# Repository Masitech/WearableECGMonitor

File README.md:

# WearableECGMonitor

Project Report (110 pages) : https://www.mahmed.tech/wp-content/uploads/2020/05/Project_Report_MAhmed-converted-compressed.pdf 

## 1.1 Background

The IoT (internet of things) field in wearable healthcare has received a lot of attention in the last
few years due to advancement in computing paradigms: cloud computing, fog computing and
edge computing. Machine learning on the cloud has revolutionized traditional healthcare.
ECG monitors is not a new concept, it has been around the medical environment for many
decades. In the last few years, technology has started appearing in many wearable devices such
as smartwatches (apple watch 4+) and dedicated standalone products such as AliveCor's
KardiaMobile[3]. Most of the designs use 3 wires: 2 wires for bipotential input and the third wire
for body bias (common-mode rejection).

## 1.2 Aim

This project aims to design a low power battery operated wearable device with wireless
capability that can measure ECG from the bipotential single channel. The system should be
lightweight and small since it will be worn for a long period without a battery recharge.
Use professional tools & software platforms to design the system which is relevant in the
embedded systems industry.
Understand low level embedded systems and overcome problems which are specific to the
project using OEM datasheet/documentation. 

## 1.3 Objective

* Small custom-designed embedded arm cortex board using small SMD parts (0603 or
smaller).

* Develop low power wearable hardware that can be powered from a small battery.

* Develop onboard battery management system for charging lipo battery.

* Implement low power wireless capability using BLE.

* Design and implement embedded firmware using RTOS

* Use of UART, SPI, PWM, SAADC, Timers and interrupts in the firmware using
low-level hardware coding and API.

* Use of commercial development software and tools.

## 1.4 Technical Requirement / Tools

During the development phase of this project, the following tools were used, and it would be
essential to have access to these tools for future continuation of the work.

Software IDE: Keil uVision 5 

JLink Debugger / STLink Programmer: Used to flash the microcontroller.

J-Flash Light v6.54 (Tool to flash hex file)

nRF Bluetooth Connect App for Bluetooth Debugging (Android)

FTDI (USB to Serial) Module - UART communication

Eagle Autodesk to modify the schematic

Embedded C++/C, JavaScript, Bluetooth GATT, Max30003 AFE, Mbed OS, nrfSDK15

Optional: Tools that can be helpful.

SamacSys PCB Library: Excellent tool to get component footprint and save time

Notepad++ : Generic text editor, highly recommended

UART serial monitor: Arduino Serial Monitor, Termite

Plotting ECG Waveform: Arduino Plotter, Windisp (Custom Tool)

Multimeter, Oscilloscope & SMD soldering skills 

## 2. System Design

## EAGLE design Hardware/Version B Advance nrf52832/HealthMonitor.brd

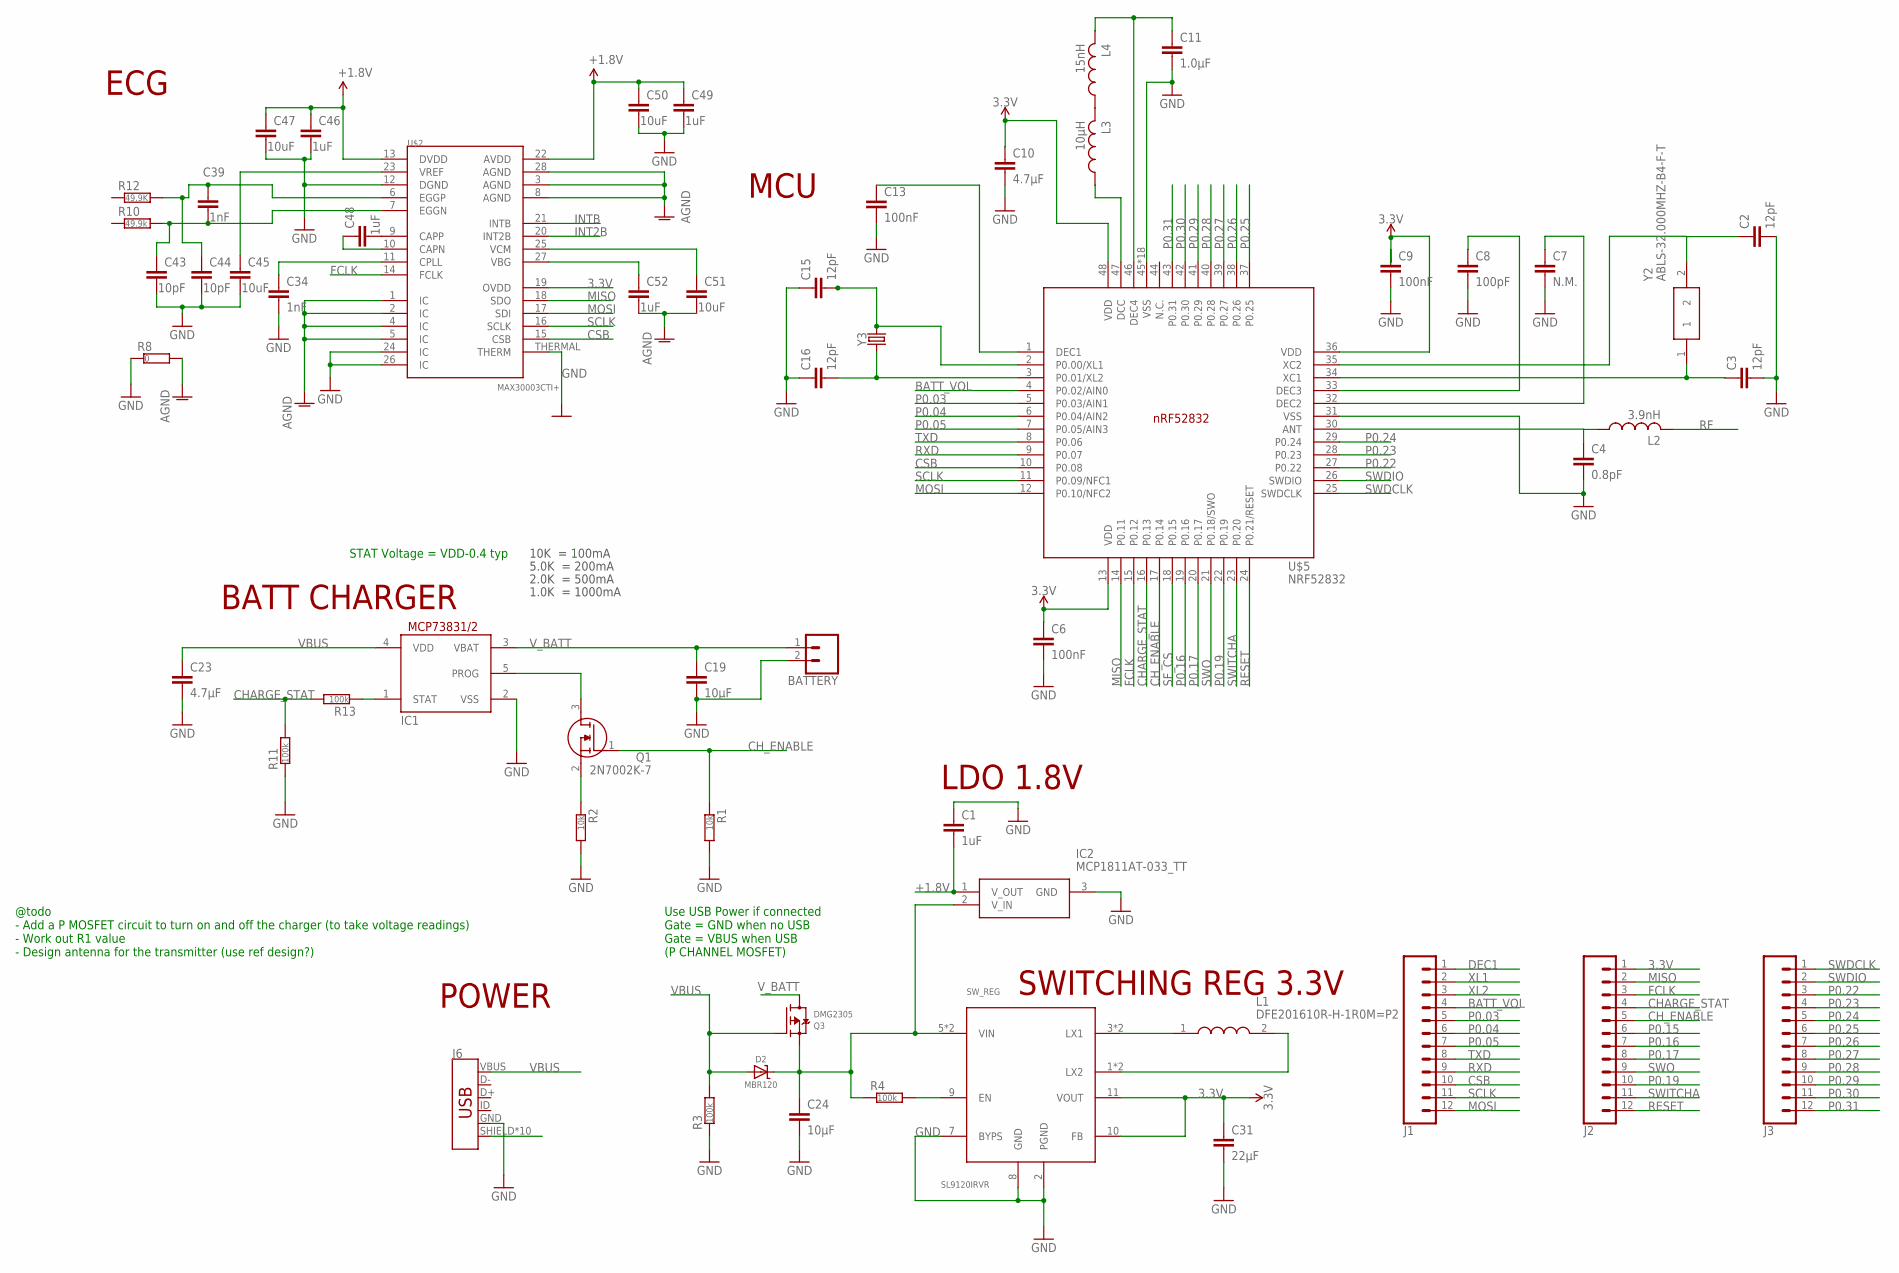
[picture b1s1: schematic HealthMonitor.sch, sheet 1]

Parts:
BATTERY: CONN_02; 1X02
C1: 1uF; RESC0603_L
C2, C3, C15, C16: 12pF; RESC0603_L
C4: 0.8pF; RESC0603_L
C6, C9, C13: 100nF; RESC0603_L
C7: N.M.; RESC0603_L
C8: 100pF; RESC0603_L
C10, C23: 4.7µF; RESC0603_N
C11: 1.0µF; RESC0603_N
C19, C24: 10µF; RESC0603_N
C31: 22µF; RESC0603_N
C34: 1nF; C0603
C39: 1nF; RESC0603_N
C43, C44: 10pF; RESC0603_N
C45, C47, C50, C51: 10uF; RESC0603_N
C46, C48, C49, C52: 1uF; RESC0603_N
D2: MBR120; SOD-123
IC1: MCP73831/OT; SOT23-5L
IC2: MCP1811AT-033_TT; SOT95P237X112-3N
J1, J2, J3: CONN_12; 1X12
J6: USB_MICRO-B_HALF_PTH_MILL; USB-MICROB-PTH-MILL
L1: DFE201610R-H-1R0M=P2; INDC2016X100N
L2: 3.9nH; RESC0402_N
L3: 10µH; RESC0603_N
L4: 15nH; RESC0402_N
Q1: 2N7002K-7; SOT96P240X100-3N
Q3: DMG2305; SOT23-R
R1, R2: 10k; RESC0603_L
R3, R4, R11, R13: 100k; RESC0603_L
R8: 0; RESC0603_L
R10: 49.9k; RESC0603_L
R12: 49.9K; RESC0603_L
SW_REG: SL9120IRVR; TQFN-12
U$2: MAX30003CTI+; QFN-28
U$5: NRF52832; QFN40P600X600X90-48_N
Y2: ABLS-32.000MHZ-B4-F-T; ABLS-12.000MHZ-B2
Y3: CRYSTALSMD-2X6; CRYSTAL-SMD-2X6-CYL

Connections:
3.3V: C6.1, C9.1, C10.1, C31.1, J2.1, SW_REG.10 (FB), SW_REG.11 (VOUT), U$2.19 (OVDD), U$5.13 (VDD), U$5.36 (VDD), U$5.48 (VDD); also elsewhere on the board
+1.8V: C1.2, C46.1, C47.1, C49.1, C50.1, IC2.1 (V_OUT), U$2.13 (DVDD), U$2.22 (AVDD); also elsewhere on the board
AGND: C51.2, C52.2, R8.2, U$2.1 (IC), U$2.2 (IC), U$2.3 (AGND), U$2.4 (IC), U$2.5 (IC), U$2.8 (AGND), U$2.28 (AGND)
BATT_VOL: J1.4, U$5.4 (P0.02/AIN0); also elsewhere on the board
CHARGE_STAT: J2.4, R11.2, R13.2, U$5.16 (P0.13)
CH_ENABLE: J2.5, Q1.1 (G), R1.1, U$5.17 (P0.14)
CSB: J1.10, U$2.15 (CSB), U$5.10 (P0.08)
DEC1: J1.1
ECGN1: C39.2, C43.1, R10.2, U$2.7 (EGGN)
ECGP1: C39.1, C44.1, R12.2, U$2.6 (EGGP)
FCLK: J2.3, U$2.14 (FCLK), U$5.15 (P0.12)
GND: BATTERY.2, C1.1, C2.2, C3.2, C4.2, C6.2, C7.2, C8.2, C9.2, C10.2, C11.2, C13.2, C15.1, C16.1, C19.2, C23.2, C24.2, C31.2, C34.2, C43.2, C44.2, C45.2, C46.2, C47.2, C49.2, C50.2, IC1.2 (VSS), IC2.3 (GND), J6.GND, R1.2, R2.2, R3.1, R8.1, R11.1, SW_REG.2 (PGND), SW_REG.7 (BYPS), SW_REG.8 (GND), U$2.12 (DGND), U$2.24 (IC), U$2.26 (IC), U$2.THERMAL (THERM), U$5.31 (VSS), U$5.45 (VSS), U$5.PAD (VSS), U$5.PAD@VIA01 (VSS), U$5.PAD@VIA02 (VSS), U$5.PAD@VIA03 (VSS), U$5.PAD@VIA04 (VSS), U$5.PAD@VIA05 (VSS), U$5.PAD@VIA06 (VSS), U$5.PAD@VIA07 (VSS), U$5.PAD@VIA08 (VSS), U$5.PAD@VIA09 (VSS), U$5.PAD@VIA10 (VSS), U$5.PAD@VIA11 (VSS), U$5.PAD@VIA12 (VSS), U$5.PAD@VIA13 (VSS), U$5.PAD@VIA14 (VSS), U$5.PAD@VIA15 (VSS), U$5.PAD@VIA16 (VSS); also elsewhere on the board
INT2B: U$2.20 (INT2B)
INTB: U$2.21 (INTB)
MISO: J2.2, U$2.18 (SDO), U$5.14 (P0.11); also elsewhere on the board
MOSI: J1.12, U$2.17 (SDI), U$5.12 (P0.10/NFC2); also elsewhere on the board
unnamed: R4.2, SW_REG.9 (EN)
unnamed: IC1.1 (STAT), R13.1
unnamed: Q1.2 (S), R2.1
unnamed: C13.1, U$5.1 (DEC1)
unnamed: L1.1, SW_REG.3 (LX1), SW_REG.4 (LX1)
unnamed: C24.1, D2.C, IC2.2 (V_IN), Q3.2 (S), R4.1, SW_REG.5 (VIN), SW_REG.6 (VIN)
unnamed: IC1.5 (PROG), Q1.3 (D)
unnamed: L1.2, SW_REG.1 (LX2), SW_REG.12 (LX2)
unnamed: C51.1, U$2.25 (VCM)
unnamed: C2.1, Y2.2
unnamed: L3.2, L4.1
unnamed: L3.1, U$5.47 (DCC)
unnamed: C16.2, U$5.3 (P0.01/XL2), Y3.X1 (1)
unnamed: C3.1, U$5.34 (XC1), Y2.1
unnamed: C4.1, L2.1
unnamed: C34.1, U$2.11 (CPLL)
unnamed: C48.1, U$2.10 (CAPN)
unnamed: C45.1, U$2.23 (VREF)
unnamed: C52.1, U$2.27 (VBG)
unnamed: C7.1, U$5.32 (DEC2)
unnamed: C48.2, U$2.9 (CAPP)
unnamed: C11.1, L4.2, U$5.46 (DEC4)
unnamed: C8.1, U$5.33 (DEC3)
P0.03: J1.5, U$5.5 (P0.03/AIN1)
P0.04: J1.6, U$5.6 (P0.04/AIN2)
P0.05: J1.7, U$5.7 (P0.05/AIN3)
P0.15: J2.6
P0.16: J2.7, U$5.19 (P0.16)
P0.17: J2.8, U$5.20 (P0.17)
P0.19: J2.10, U$5.22 (P0.19)
P0.22: J3.3, U$5.27 (P0.22)
P0.23: J3.4, U$5.28 (P0.23)
P0.24: J3.5, U$5.29 (P0.24)
P0.25: J3.6, U$5.37 (P0.25)
P0.26: J3.7, U$5.38 (P0.26)
P0.27: J3.8, U$5.39 (P0.27)
P0.28: J3.9, U$5.40 (P0.28)
P0.29: J3.10, U$5.41 (P0.29)
P0.30: J3.11, U$5.42 (P0.30)
P0.31: J3.12, U$5.43 (P0.31)
RESET: J2.12, U$5.24 (P0.21/RESET); also elsewhere on the board
RF: L2.2
RXD: J1.9, U$5.9 (P0.07); also elsewhere on the board
SCLK: J1.11, U$2.16 (SCLK), U$5.11 (P0.09/NFC1); also elsewhere on the board
SF_CS: U$5.18 (P0.15); also elsewhere on the board
SHIELD: J6.SHIELD, J6.SHIELD2 (SHIELD), J6.SHIELD3 (SHIELD), J6.SHIELD4 (SHIELD), J6.SHIELD5 (SHIELD), J6.SHIELD6 (SHIELD), J6.SHIELD7 (SHIELD), J6.SHIELD8 (SHIELD), J6.SHIELD9 (SHIELD), J6.SHIELD10 (SHIELD)
SWDCLK: J3.1, U$5.25 (SWDCLK)
SWDIO: J3.2, U$5.26 (SWDIO); also elsewhere on the board
SWITCHA: J2.11, U$5.23 (P0.20); also elsewhere on the board
SWO: J2.9, U$5.21 (P0.18/SWO)
TXD: J1.8, U$5.8 (P0.06); also elsewhere on the board
VBUS: C23.1, D2.A, IC1.4 (VDD), J6.VBUS, Q3.1 (G), R3.2
V_BATT: BATTERY.1, C19.1, IC1.3 (VBAT), Q3.3 (D); also elsewhere on the board
XL1: C15.2, J1.2, U$5.2 (P0.00/XL1), Y3.X2 (2)
XL2: J1.3

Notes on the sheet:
10K = 100mA
5.0K = 200mA
2.0K = 500mA
1.0K = 1000mA
Use USB Power if connected Gate = GND when no USB Gate = VBUS when USB (P CHANNEL MOSFET)
ECG
STAT Voltage = VDD-0.4 typ
@todo - Add a P MOSFET circuit to turn on and off the charger (to take voltage readings) - Work out R1 value - Design antenna for the transmitter (use ref design?)
POWER
BATT CHARGER
LDO 1.8V
SWITCHING REG 3.3V
MCU

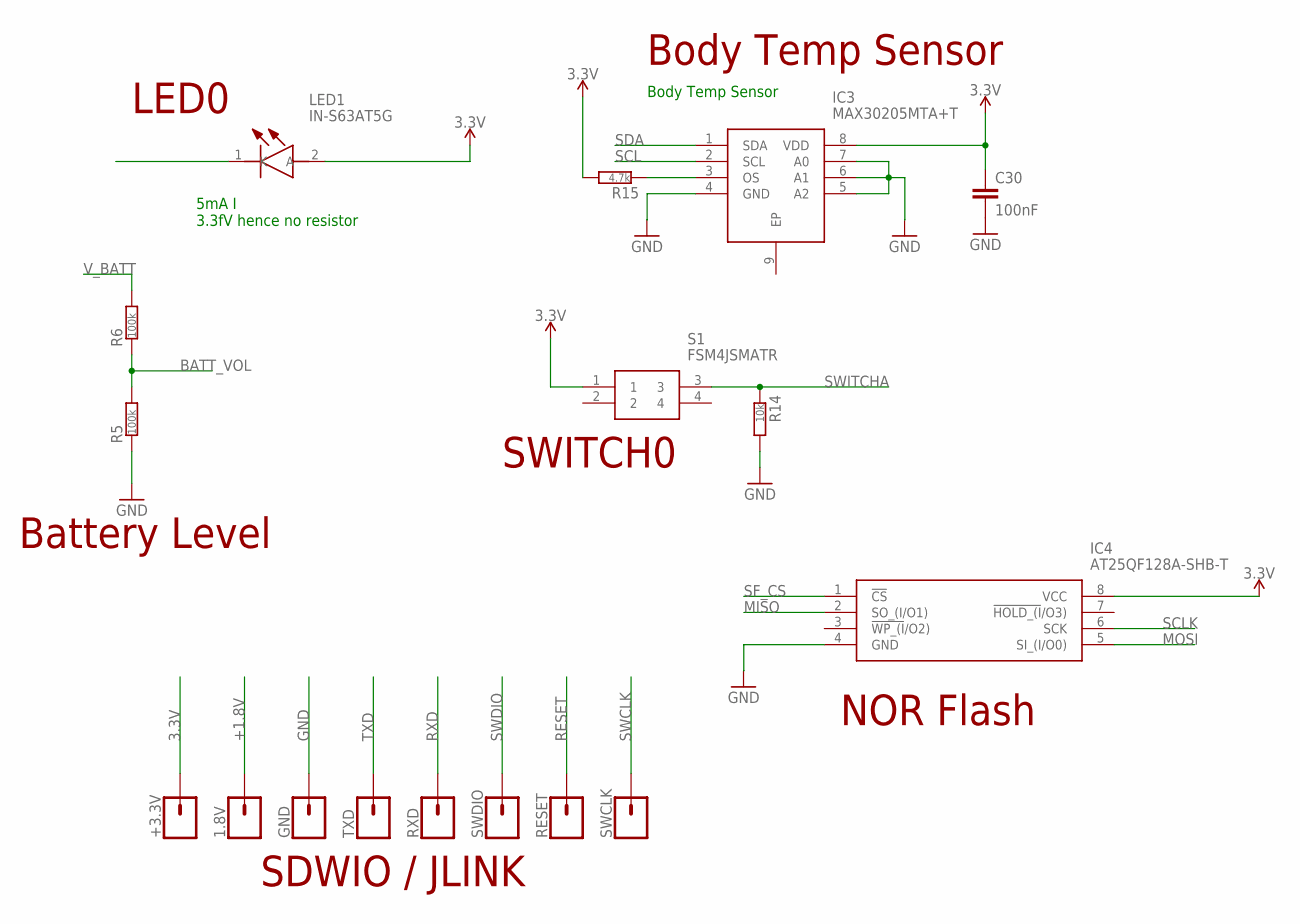
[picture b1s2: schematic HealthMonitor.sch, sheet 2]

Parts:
1.8V: CONN_01; 1X01
+3.3V: CONN_01; 1X01
C30: 100nF; RESC0603_L
GND: CONN_01; 1X01
IC3: MAX30205MTA+T; SON65P300X300X80-9N
IC4: AT25QF128A-SHB-T; SOIC127P790X216-8N
LED1: IN-S63AT5G; LEDM168X39N
R5, R6: 100k; RESC0603_L
R14: 10k; RESC0603_L
R15: 4.7k; RESC0603_L
RESET: CONN_01; 1X01
RXD: CONN_01; 1X01
S1: FSM4JSMATR
SWCLK: CONN_01; 1X01
SWDIO: CONN_01; 1X01
TXD: CONN_01; 1X01

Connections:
3.3V: +3.3V.1, C30.1, IC3.8 (VDD), IC4.8 (VCC), LED1.2 (A), R15.2, S1.1; also elsewhere on the board
+1.8V: 1.8V.1; also elsewhere on the board
BATT_VOL: R5.2, R6.1; also elsewhere on the board
GND: C30.2, GND.1, IC3.4 (GND), IC3.5 (A2), IC3.6 (A1), IC3.7 (A0), IC4.4 (GND), R5.1, R14.2; also elsewhere on the board
LEDA: LED1.1 (K)
MISO: IC4.2 (SO_(I/O1)); also elsewhere on the board
MOSI: IC4.5 (SI_(I/O0)); also elsewhere on the board
unnamed: IC3.3 (OS), R15.1
RESET: RESET.1; also elsewhere on the board
RXD: RXD.1; also elsewhere on the board
SCL: IC3.2 (SCL)
SCLK: IC4.6 (SCK); also elsewhere on the board
SDA: IC3.1 (SDA)
SF_CS: IC4.1 (!CS); also elsewhere on the board
SWCLK: SWCLK.1
SWDIO: SWDIO.1; also elsewhere on the board
SWITCHA: R14.1, S1.3; also elsewhere on the board
TXD: TXD.1; also elsewhere on the board
V_BATT: R6.2; also elsewhere on the board

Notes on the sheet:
Body Temp Sensor
5mA I 3.3fV hence no resistor
Battery Level
LED0
SWITCH0
Body Temp Sensor
NOR Flash
SDWIO / JLINK

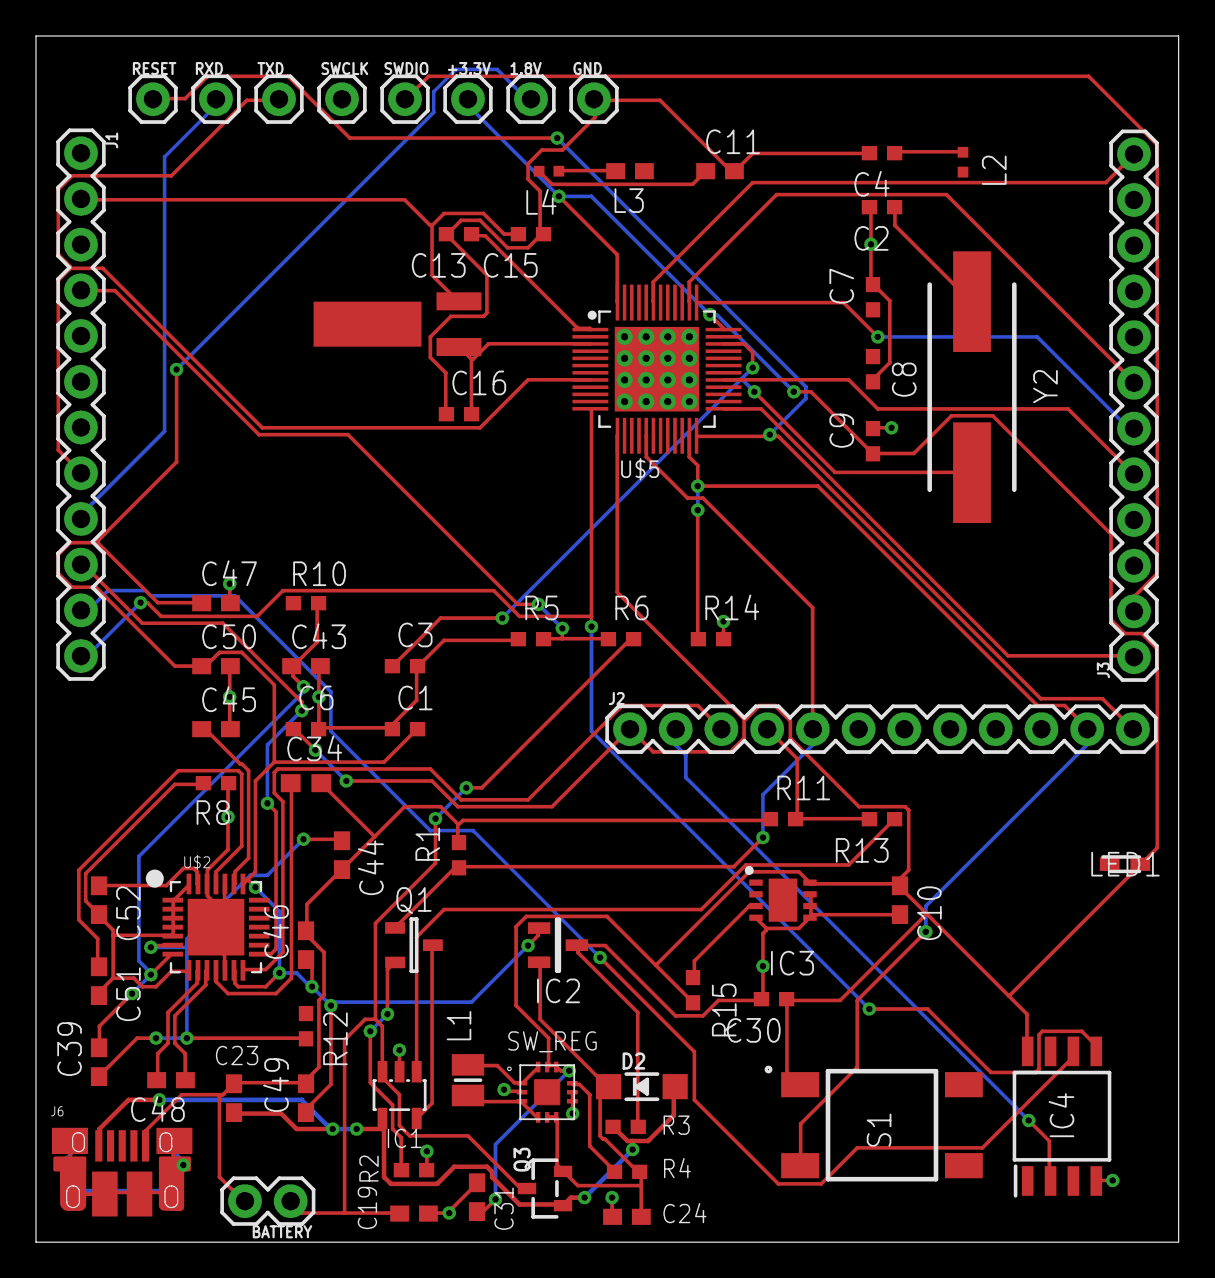
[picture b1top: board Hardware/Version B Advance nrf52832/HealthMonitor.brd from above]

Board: 2 copper layers, 63.5 x 67.0 mm, 74 parts (0 on the bottom side), 66 nets.

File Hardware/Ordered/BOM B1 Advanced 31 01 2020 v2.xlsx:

No. | Qty | Value | Package | Parts | Description | No. | Supplier | Order Code | Price / MOQ | MOQ | To Order Amount | Price Order | Value | Device
1 | 14 |  |  |  |  | 1 |  |  |  |  |  |  |  | RESISTOR
2 | 1 | 0R | RESC0603_N | R8 | Generic chip resistor | 2 | Farnell | 1469739 | 0.17 | 10 | 10 | 0.17 | 0R | RESISTOR_0603_N
3 | 6 | 100k | RESC0603_N | R3, R4, R5, R6, R11, R13 | Generic chip resistor | 3 | Farnell | 2447226 | 0.04 | 10 | 10 | 0.04 | 100k | RESISTOR_0603_N
4 | 3 | 10k | RESC0603_N | R1, R2, R14 | Generic chip resistor | 4 | Farnell | 2447230 | 0.04 | 10 | 10 | 0.04 | 10k | RESISTOR_0603_N
5 | 1 | 4.7k | RESC0603_N | R15 | Generic chip resistor | 5 | Farnell | 2694880 | 0.04 | 10 | 10 | 0.04 | 4.7k | RESISTOR_0603_N
6 | 2 | 49.9K | RESC0603_N | R12 | Generic chip resistor | 6 | Farnell | 2447380 | 0.05 | 10 | 10 | 0.05 | 49.9K | RESISTOR_0603_N
7 | 1 | 60R (56Ohms) | RESC0603_N | R7 | Generic chip resistor | 7 | Farnell | 2447400 | 0.05 | 10 | 10 | 0.05 | 60R (56Ohms) | RESISTOR_0603_N
8 | 29 |  |  |  |  | 8 | Farnell |  |  |  |  |  |  | CAPACITOR
9 | 1 | 0.8pF (5%) | RESC0603_N | C4 | Generic chip capacitor | 9 | Mouser | 609-251R14S0R8AV4T | 0.3 | 1 | 5 | 1.5 | 0.8pF (5%) | CAPACITOR_0603_N
10 | 4 | 100nF | RESC0603_N | C6, C9, C13, C30 | Generic chip capacitor | 10 | Farnell | 2429362 | 0.13 | 10 | 10 | 0.13 | 100nF | CAPACITOR_0603_N
11 | 1 | 100pF | RESC0603_N | C8 | Generic chip capacitor | 11 | Farnell | 2896358 | 0.18 | 10 | 10 | 0.18 | 100pF | CAPACITOR_0603_N
12 | 2 | 10pF | RESC0603_N | C43, C44 | Generic chip capacitor | 12 | Farnell | 2496879 | 0.28000000000000003 | 10 | 10 | 0.28000000000000003 | 10pF | CAPACITOR_0603_N
13 | 6 | 10uF | RESC0603_N | C45, C47, C50, C51,C19, C24 | Generic chip capacitor | 13 | Farnell | 2494233 | 1.33 | 10 | 10 | 1.33 | 10uF | CAPACITOR_0603_N
14 | 4 | 12pF (2%) | RESC0603_N | C2, C3, C15, C16 | Generic chip capacitor | 14 | Farnell | 2896365 | 0.67 | 10 | 10 | 0.67 | 12pF (2%) | CAPACITOR_0603_N
15 | 2 | 1nF | RESC0603_N | C5, C39 | Generic chip capacitor | 15 | Farnell | 2524816 | 0.32 | 10 | 10 | 0.32 | 1nF | CAPACITOR_0603_N
16 | 6 | 1uF | RESC0603_N | C1, C11, C46, C48, C49, C52 | Generic chip capacitor | 16 | Farnell | 9227776 | 0.32 | 10 | 10 | 0.32 | 1uF | CAPACITOR_0603_N
17 | 1 | 22µF | RESC0603_N | C31 | Generic chip capacitor | 17 | Farnell | 1845732 | 1.0900000000000001 | 10 | 10 | 1.0900000000000001 | 22µF | CAPACITOR_0603_N
18 | 2 | 4.7µF | RESC0603_N | C10, C23 | Generic chip capacitor | 18 | Farnell | 3013399 | 0.53 | 10 | 10 | 0.53 | 4.7µF | CAPACITOR_0603_N
19 | 4 |  |  |  |  | 19 |  |  |  |  |  |  |  | INDUCTOR
20 | 1 | 10uH (>50mA) | RESC0603_N | L3 | Generic chip inductor | 20 | Farnell | 2215650 | 0.47 | 5 | 5 | 0.47 | 10uH (>50mA) | INDUCTOR_0603_N
21 | 1 | 15nH | RESC0603_N | L4 | Generic chip inductor | 21 | Farnell | 2858912 | 0.47 | 5 | 5 | 0.47 | 15nH | INDUCTOR_0603_N
22 | 1 | 3.9nH | RESC0603_N | L2 | Generic chip inductor | 22 | Farnell | 1515389 | 1.4 | 10 | 10 | 1.4 | 3.9nH | INDUCTOR_0603_N
23 | 1 | DFE201610R-H-1R0M=P2 | INDC2016X100N | L1 | DFE201610R Series Inductor 1.0uH +/-20% 0806 (2016) | 23 | Mouser | 81-DFE201610RH1R0MP2 | 0.34 | 1 | 2 | 0.68 | DFE201610R-H-1R0M=P2 | DFE201610R-H-1R0M=P2
24 | 3 |  |  |  |  | 24 |  |  |  |  |  |  |  | DIODE
25 | 1 | IN-S63AT5G | LEDM168X39N | LED1 | Standard LEDs - SMD True Green LED | 25 | Mouser | 743-IN-S63AT5G | 0.09 | 1 | 5 | 0.45 | IN-S63AT5G | IN-S63AT5G
26 |  |  |  |  |  | 26 |  |  |  |  |  |  |  | TRANSISITORS
27 | 1 | DMG2305 | SOT23-R | Q3 | P-Channel Mosfet | 27 | Farnell | 2543532 | 1.2 | 5 | 5 | 1.2 | DMG2305 | MOSFET-P
28 | 1 | 2N7002K-7 | SOT96P240X100-3N | Q1 | N-CHANNEL ENHANCEMENT MODE MOSFET | 28 |  | 1713825 | 0.67 | 5 | 5 | 0.67 | 2N7002K-7 | 2N7002K-7
29 | 2 |  |  |  |  | 29 |  |  | £ |  |  | £ |  | CRYSTAL
30 | 1 | ABM8G-12.000MHZ-4Y-T3 | ABM8G16000MHZB4YT | Y3 | Abracon 12MHz Crystal Unit +/-30ppm SMD 4-Pin 3.2 x 2.5 x 1mm | 30 | Mouser | 815-ABM8G-106-12-T | 0.4 | 1 | 5 | 2 | 815-ABM8G-106-12-T | ABM8G-12.000MHZ-4Y-T3
31 | 1 | ABS07-166-32.768KHZ-T | ABS0716632768KHZT OR 449-LFXTAL009678REEL | Y1 | Crystal IOT 32.786KHz XTAL 10ppm | 31 | Mouser | 815-ABS0716632.768KT | 0.51 | 1 | 5 | 2.5499999999999998 | ABS07-166-32.768KHZ-T | 32.768KHZ
32 | 8 |  |  |  |  | 32 |  |  |  |  |  |  |  | IC
33 | 1 | NRF52832 | QFN40P600X600X90-48_N | MCU | nRF52832 | 33 | Mouser | 949-NRF52832-QFAB-R | 4.13 | 1 | 3 | 12.39 | NRF52832 | NRF52832
34 | 1 | MAX30003CTI+ | QFN-28 | ECG |  | 34 | Farnell | 2668156 | 4.96 | 1 | 3 | 14.88 | MAX30003CTI+ | MAX30003
35 | 1 | MAX30205MTA+T | SON65P300X300X80-9N | IC3 | Human Body Temperature Sensor, 8 TDFN-EP | 35 | Farnell | 2668518 | 1.89 | 1 | 1 | 1.89 | MAX30205MTA+T | MAX30205MTA+T
36 | 1 | MBR120 | SOD-123 | D2 |  | 36 | Farnell | 1431041 | 0.28999999999999998 | 1 | 3 | 0.28999999999999998 | MBR120 | DIODE-SCHOTTKYSOD-123
37 | 1 | MCP1811AT-033_TT | SOT95P237X112-3N | IC2 | LDO Voltage Regulators Ultra Low Iq LDO | 37 | Farnell | 2990197 | 0.2 | 1 | 3 | 0.2 | MCP1811AT-033_TT | MCP1811AT-033_TT
38 | 1 | MCP73831/OT | SOT23-5L | IC1 | MCP73831/2 | 38 | Farnell | 2920755 | 0.42 | 1 | 1 | 0.42 | MCP73831/OT | MCP73831/OT
39 | 1 | AT25QF128A-SHB-T | SOIC127P790X216-8N | IC4 | NOR Flash 128Mb, 133MHz, QPI,8-SOIC-W, IND TEMP, 2.7-3.6V, T&R | 39 | Mouser | 988-AT25QF128A-SHB-T | 1.18 | 1 | 1 | 1.18 | AT25QF128A-SHB-T | AT25QF128A-SHB-T
40 | 1 | ISL9120IRTNZ | TQFN-12 | SWREG |  | 40 | Farnell | 2630543 | 1.73 | 1 | 1 | 1.73 | ISL9120IRTNZ | SWITCH REG 3.3V Fixed
41 | 2 |  |  |  |  | 41 |  |  |  |  |  |  |  | OTHER
42 | 1 | Button | PTS810SJG250SMTRLFS | S2 | IP40 Black Button Tactile Switch, SPST-NO 50 mA 3mm Surface Mount | 42 | Farnell | 3023215 | 0.96 | 10 | 10 | 0.96 | PTS810SJK250SMTRLFS | Button
43 | 1 | Micro USB | 101181940011LF | J1 | Power to the Board MICRO USD B-TYPE | 43 | Mouser | 649-10118194-0011LF | 0.31 | 1 | NULL | 0 | 10118194-0011LF | Micro USB
44 |  |  |  |  |  | 44 |  |  | 27.16 |  |  | 50.57

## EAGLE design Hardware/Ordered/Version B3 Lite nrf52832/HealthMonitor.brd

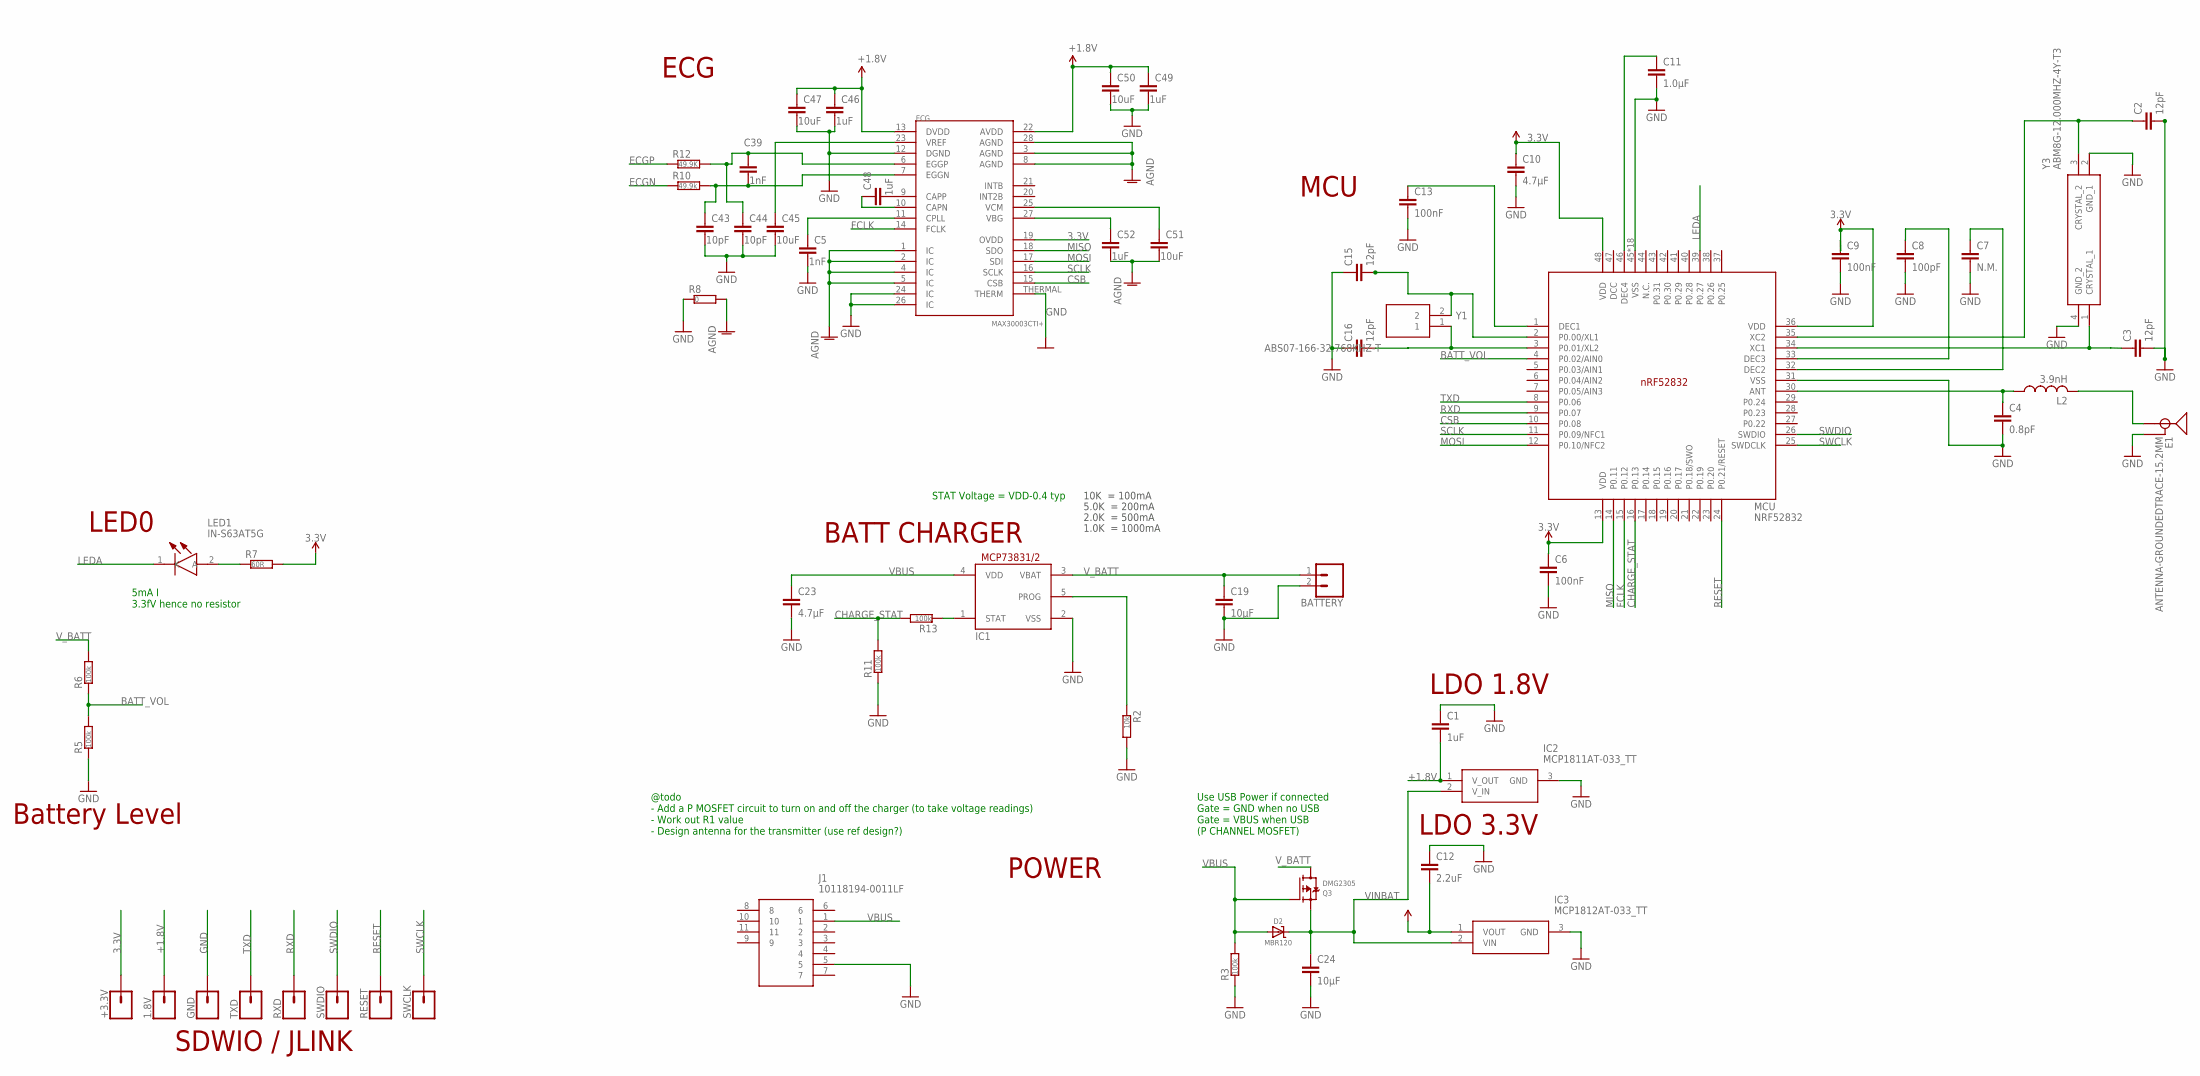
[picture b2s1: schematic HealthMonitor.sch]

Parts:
1.8V: CONN_01; 1X01
+3.3V: CONN_01; 1X01
BATTERY: CONN_02; 1X02
C1, C46, C48, C49, C52: 1uF; RESC0603_N
C2, C3, C15, C16: 12pF; RESC0603_N
C4: 0.8pF; RESC0603_N
C5, C39: 1nF; RESC0603_N
C6, C9, C13: 100nF; RESC0603_N
C7: N.M.; RESC0603_N
C8: 100pF; RESC0603_N
C10, C23: 4.7µF; RESC0603_N
C11: 1.0µF; RESC0603_N
C12: 2.2uF; RESC0603_N
C19, C24: 10µF; RESC0603_N
C43, C44: 10pF; RESC0603_N
C45, C47, C50, C51: 10uF; RESC0603_N
D2: MBR120; SOD-123
E1: ANTENNA-GROUNDEDTRACE-15.2MM; TRACE_ANTENNA_2.4GHZ_15.2MM
ECG: MAX30003CTI+; QFN-28
GND: CONN_01; 1X01
IC1: MCP73831/OT; SOT23-5L
IC2: MCP1811AT-033_TT; SOT95P237X112-3N@1
IC3: MCP1812AT-033_TT; SOT95P237X112-3N
J1: 10118194-0011LF; 101181940011LF
L2: 3.9nH; RESC0603_N
LED1: IN-S63AT5G; LEDM168X39N
MCU: NRF52832; QFN40P600X600X90-48_N
Q3: DMG2305; SOT23-R
R2: 10k; RESC0603_N
R3, R5, R6, R11, R13: 100k; RESC0603_N
R7: 60R; RESC0603_N
R8: 0; RESC0603_N
R10: 49.9k; RESC0603_N
R12: 49.9K; RESC0603_N
RESET: CONN_01; 1X01
RXD: CONN_01; 1X01
SWCLK: CONN_01; 1X01
SWDIO: CONN_01; 1X01
TXD: CONN_01; 1X01
Y1: ABS07-166-32.768KHZ-T; ABS0716632768KHZT
Y3: ABM8G-12.000MHZ-4Y-T3; ABM8G16000MHZB4YT

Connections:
3.3V: +3.3V.1, C6.1, C9.1, C10.1, C12.2, ECG.19 (OVDD), IC3.1 (VOUT), MCU.13 (VDD), MCU.36 (VDD), MCU.48 (VDD), R7.2
+1.8V: 1.8V.1, C1.2, C46.1, C47.1, C49.1, C50.1, ECG.13 (DVDD), ECG.22 (AVDD), IC2.1 (V_OUT)
AGND: C51.2, C52.2, ECG.1 (IC), ECG.2 (IC), ECG.3 (AGND), ECG.4 (IC), ECG.5 (IC), ECG.8 (AGND), ECG.28 (AGND), R8.2
BATT_VOL: MCU.4 (P0.02/AIN0), R5.2, R6.1
CHARGE_STAT: MCU.16 (P0.13), R11.2, R13.2
CSB: ECG.15 (CSB), MCU.10 (P0.08)
ECGN: R10.1
ECGN1: C39.2, C43.1, ECG.7 (EGGN), R10.2
ECGP: R12.1
ECGP1: C39.1, C44.1, ECG.6 (EGGP), R12.2
FCLK: ECG.14 (FCLK), MCU.15 (P0.12)
GND: BATTERY.2, C1.1, C2.2, C3.2, C4.2, C5.2, C6.2, C7.2, C8.2, C9.2, C10.2, C11.2, C12.1, C13.2, C15.1, C16.1, C19.2, C23.2, C24.2, C43.2, C44.2, C45.2, C46.2, C47.2, C49.2, C50.2, E1.GND, ECG.12 (DGND), ECG.24 (IC), ECG.26 (IC), ECG.THERMAL (THERM), GND.1, IC1.2 (VSS), IC2.3 (GND), IC3.3 (GND), J1.5, MCU.31 (VSS), MCU.45 (VSS), MCU.PAD (VSS), MCU.PAD@VIA01 (VSS), MCU.PAD@VIA02 (VSS), MCU.PAD@VIA03 (VSS), MCU.PAD@VIA04 (VSS), MCU.PAD@VIA05 (VSS), MCU.PAD@VIA06 (VSS), MCU.PAD@VIA07 (VSS), MCU.PAD@VIA08 (VSS), MCU.PAD@VIA09 (VSS), MCU.PAD@VIA10 (VSS), MCU.PAD@VIA11 (VSS), MCU.PAD@VIA12 (VSS), MCU.PAD@VIA13 (VSS), MCU.PAD@VIA14 (VSS), MCU.PAD@VIA15 (VSS), MCU.PAD@VIA16 (VSS), R2.2, R3.1, R5.1, R8.1, R11.1, Y3.2 (GND_1), Y3.4 (GND_2)
LEDA: LED1.1 (K), MCU.39 (P0.27)
MISO: ECG.18 (SDO), MCU.14 (P0.11)
MOSI: ECG.17 (SDI), MCU.12 (P0.10/NFC2)
unnamed: IC1.5 (PROG), R2.1
unnamed: IC1.1 (STAT), R13.1
unnamed: C13.1, MCU.1 (DEC1)
unnamed: LED1.2 (A), R7.1
unnamed: C11.1, MCU.46 (DEC4)
unnamed: C51.1, ECG.25 (VCM)
unnamed: C16.2, MCU.3 (P0.01/XL2), Y1.1
unnamed: C3.1, MCU.34 (XC1), Y3.1 (CRYSTAL_1)
unnamed: C4.1, L2.1, MCU.30 (ANT)
unnamed: E1.ANT (SIGNAL), L2.2
unnamed: C5.1, ECG.11 (CPLL)
unnamed: C48.1, ECG.10 (CAPN)
unnamed: C45.1, ECG.23 (VREF)
unnamed: C52.1, ECG.27 (VBG)
unnamed: C7.1, MCU.32 (DEC2)
unnamed: C48.2, ECG.9 (CAPP)
unnamed: C2.1, MCU.35 (XC2), Y3.3 (CRYSTAL_2)
unnamed: C8.1, MCU.33 (DEC3)
RESET: MCU.24 (P0.21/RESET), RESET.1
RXD: MCU.9 (P0.07), RXD.1
SCLK: ECG.16 (SCLK), MCU.11 (P0.09/NFC1)
SWCLK: MCU.25 (SWDCLK), SWCLK.1
SWDIO: MCU.26 (SWDIO), SWDIO.1
TXD: MCU.8 (P0.06), TXD.1
VBUS: C23.1, D2.A, IC1.4 (VDD), J1.1, Q3.1 (G), R3.2
VINBAT: C24.1, D2.C, IC2.2 (V_IN), IC3.2 (VIN), Q3.2 (S)
V_BATT: BATTERY.1, C19.1, IC1.3 (VBAT), Q3.3 (D), R6.2
XL1: C15.2, MCU.2 (P0.00/XL1), Y1.2

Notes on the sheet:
10K = 100mA
5.0K = 200mA
2.0K = 500mA
1.0K = 1000mA
Use USB Power if connected Gate = GND when no USB Gate = VBUS when USB (P CHANNEL MOSFET)
STAT Voltage = VDD-0.4 typ
@todo - Add a P MOSFET circuit to turn on and off the charger (to take voltage readings) - Work out R1 value - Design antenna for the transmitter (use ref design?)
POWER
BATT CHARGER
LDO 1.8V
ECG
MCU
LDO 3.3V
5mA I 3.3fV hence no resistor
Battery Level
LED0
SDWIO / JLINK

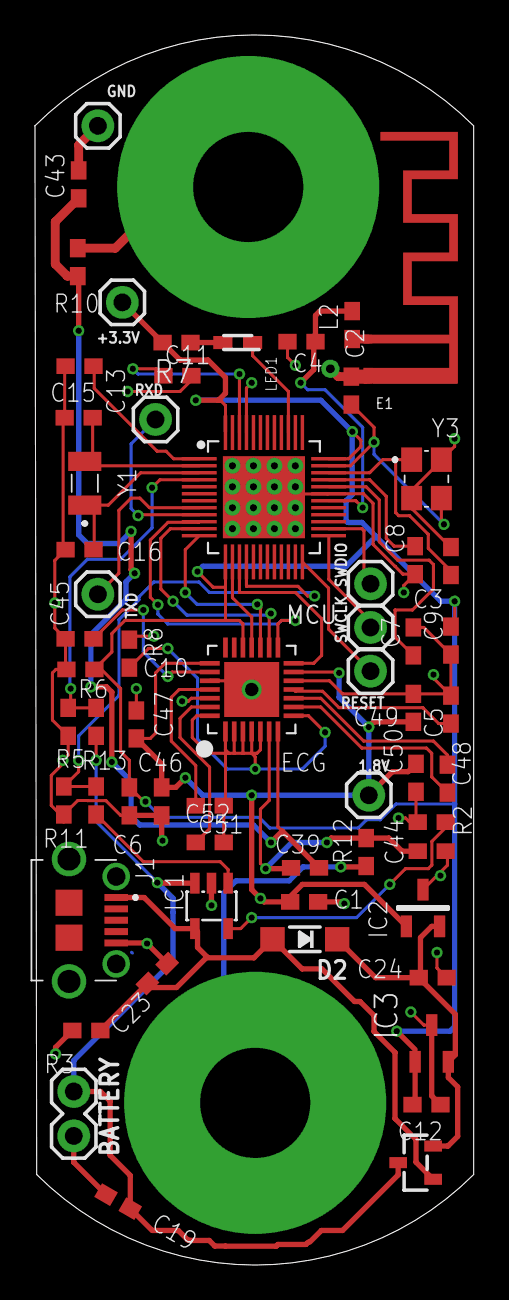
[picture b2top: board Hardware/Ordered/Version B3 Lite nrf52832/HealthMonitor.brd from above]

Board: 2 copper layers, 25.1 x 70.4 mm, 61 parts (1 on the bottom side), 41 nets.

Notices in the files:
parts and their libraries:
microbuilder: This work is placed in the public domain, and may be freely used for commercial and non-commercial work with the following conditions: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
SparkFun-Connectors: Licensing: Creative Commons ShareAlike 4.0 International - https://creativecommons.org/licenses/by-sa/4.0
